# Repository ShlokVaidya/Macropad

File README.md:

# Custom Macropad  

## 🚀 Overview  
This project is a custom macropad featuring a 4x3 keyboard, 1 rotary encoders.  

## 📂 Repository Structure  
```
📁 PCB/   # KiCad PCB and schematic files
📁 docs/  # PDFs, images, and additional documentation
📁SILK/ # Logos
```
How I Built My Macropad

I designed this macropad by following a mix of online tutorials and Hack Club Blueprint resources. I first watched a few PCB design tutorials to understand how keyboard matrices, diodes, switches, and microcontrollers work together. Using those as a base, I modified the designs to match my needs — including customizing the number of keys, the layout, and the placement of the microcontroller.

- My Process

1. Research & Tutorials
I watched tutorials on KiCad basics, PCB routing, switch footprints, diode direction, and USB power protection. These helped me understand the standard keyboard wiring patterns.

2. Creating the Schematic
I made the key matrix using rows, columns, and diodes. I connected everything to the microcontroller pins according to the firmware requirements.

3. Designing the PCB Layout
Using the tutorials as reference, I arranged the switches, added stabilizing holes, routed traces, and made sure the USB and microcontroller connections followed good design practices.

4. Modifying for My Needs
I changed the layout spacing, optimized the routing, and adapted the components to the specific features I wanted in my macropad.
This included switching some pin assignments, adjusting diode placement, and improving the routing flow.

5. Final Checks
I ran ERC/DRC checks, compared my layout against multiple tutorial examples, and manually verified diode orientation and USB connections.

- Challenges I Faced

1. Learning proper keyboard matrix wiring and diode direction

2. Understanding how to route clean traces without crossing

3. Figuring out microcontroller pin assignments

4. Managing the spacing between switches

5. Ensuring USB and power connections were correct

Plans Ahead

I will start the 3D model design on December 15th

- I will then generate STL files, export renders, and add them to the README

### BOM

Cost:- https://www.digikey.in/short/rrz541t3
Spent around 6 hours around designing the pcb!

NOTE TO THE REVIEWER:
1. I have my exams upcoming so there might be a delay in designing and uploading the 3d model
2. Requesting to check the pcb connections 
3. I live in India and many parts are either not available or overpriced, it would br better if the blueprint team ship the components and pcb. No funding required them.
4. Pls do initiate tickets as I need to buy tools for the hackpad.
5. Just verify the PCB files...

Thank you,
Shlok vaidya

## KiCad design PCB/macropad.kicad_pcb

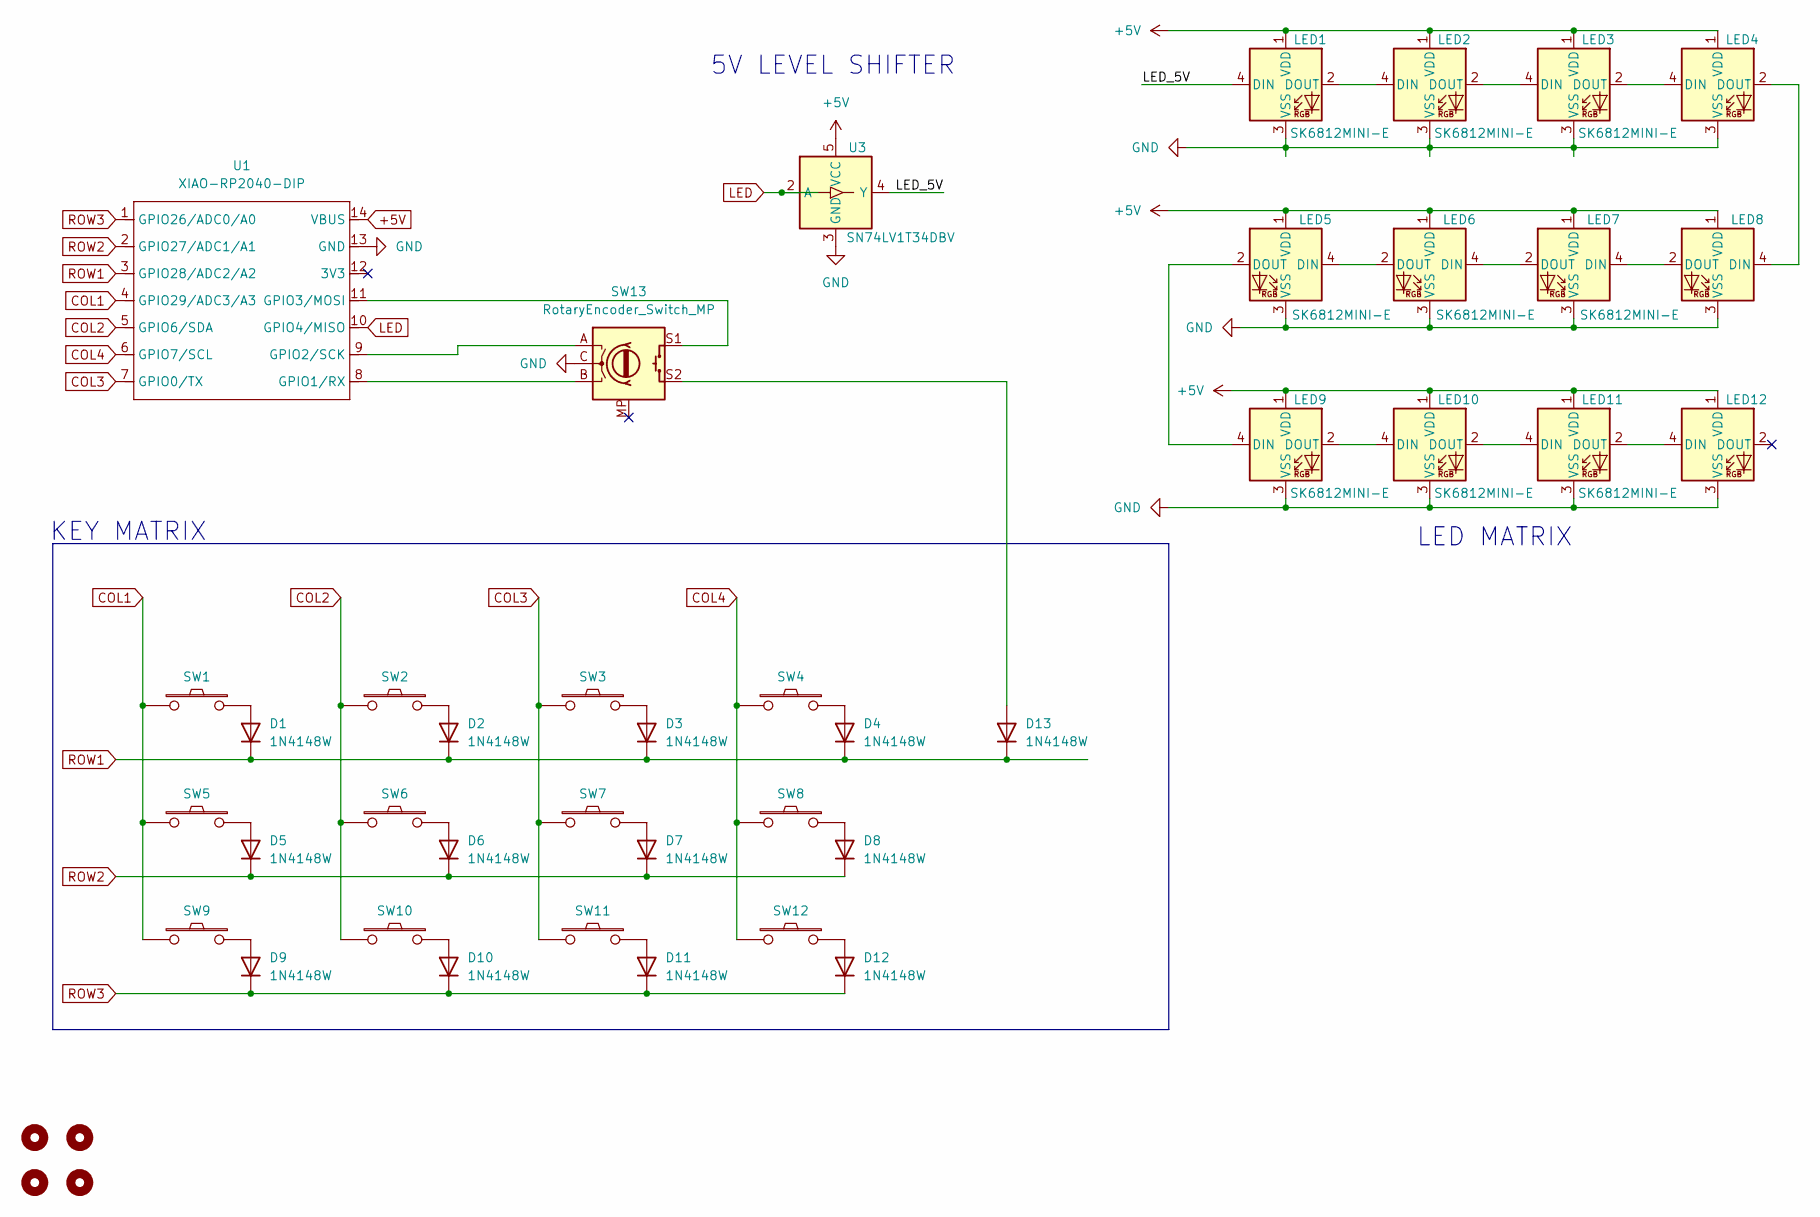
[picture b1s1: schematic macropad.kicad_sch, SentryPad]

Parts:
D1, D2, D3, D4, D5, D6, D7, D8, D9, D10, D11, D12, D13: 1N4148W; D_DO-35_SOD27_P7.62mm_Horizontal; DigiKey Part Number 1N4148W
H1, H2, H3, H4: MountingHole; Mounting_Wuerth_WA-SMSI-M3_H16mm_9774160360
LED1, LED2, LED3, LED4, LED5, LED6, LED7, LED8, LED9, LED10, LED11, LED12: SK6812MINI-E; MX_SK6812MINI-E_REV; DigiKey Part Number 1528-4960-ND
SW1, SW2, SW3, SW4, SW5, SW6, SW7, SW8, SW9, SW10, SW11, SW12: keyswitch; SW_Cherry_MX_1.00u_PCB; DigiKey Part Number MX2A-11NA
SW13: RotaryEncoder_Switch_MP; RotaryEncoder_Alps_EC11E-Switch_Vertical_H20mm
U1: XIAO-RP2040-DIP
U3: SN74LV1T34DBV; SOT-23-5; DigiKey Part Number SN74LV1T34DBV

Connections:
+5V: LED1.1 (VDD), LED2.1 (VDD), LED3.1 (VDD), LED4.1 (VDD), LED5.1 (VDD), LED6.1 (VDD), LED7.1 (VDD), LED8.1 (VDD), LED9.1 (VDD), LED10.1 (VDD), LED11.1 (VDD), LED12.1 (VDD), U1.14 (VBUS), U3.5 (VCC)
/LED_5V: LED1.4 (DIN), U3.4 (Y)
COL1: SW1.2, SW5.2, SW9.2, U1.4 (GPIO29/ADC3/A3)
COL2: SW2.2, SW6.2, SW10.2, U1.5 (GPIO6/SDA)
COL3: SW3.2, SW7.2, SW11.2, U1.7 (GPIO0/TX)
COL4: SW4.2, SW8.2, SW12.2, U1.6 (GPIO7/SCL)
GND: LED1.3 (VSS), LED2.3 (VSS), LED3.3 (VSS), LED4.3 (VSS), LED5.3 (VSS), LED6.3 (VSS), LED7.3 (VSS), LED8.3 (VSS), LED9.3 (VSS), LED10.3 (VSS), LED11.3 (VSS), LED12.3 (VSS), SW13.C, U1.13 (GND), U3.3 (GND)
LED: U1.10 (GPIO4/MISO), U3.2 (A)
unnamed: D1.2 (A), SW1.1
unnamed: D2.2 (A), SW2.1
unnamed: D3.2 (A), SW3.1
unnamed: D4.2 (A), SW4.1
unnamed: D5.2 (A), SW5.1
unnamed: D6.2 (A), SW6.1
unnamed: D7.2 (A), SW7.1
unnamed: D8.2 (A), SW8.1
unnamed: D9.2 (A), SW9.1
unnamed: D10.2 (A), SW10.1
unnamed: D11.2 (A), SW11.1
unnamed: D12.2 (A), SW12.1
unnamed: D13.2 (A), SW13.S2
unnamed: LED1.2 (DOUT), LED2.4 (DIN)
unnamed: LED2.2 (DOUT), LED3.4 (DIN)
unnamed: LED3.2 (DOUT), LED4.4 (DIN)
unnamed: LED4.2 (DOUT), LED8.4 (DIN)
unnamed: LED5.4 (DIN), LED6.2 (DOUT)
unnamed: LED5.2 (DOUT), LED9.4 (DIN)
unnamed: LED6.4 (DIN), LED7.2 (DOUT)
unnamed: LED7.4 (DIN), LED8.2 (DOUT)
unnamed: LED9.2 (DOUT), LED10.4 (DIN)
unnamed: LED10.2 (DOUT), LED11.4 (DIN)
unnamed: LED11.2 (DOUT), LED12.4 (DIN)
unnamed: SW13.B, U1.8 (GPIO1/RX)
unnamed: SW13.A, U1.9 (GPIO2/SCK)
unnamed: SW13.S1, U1.11 (GPIO3/MOSI)
ROW1: D1.1 (K), D2.1 (K), D3.1 (K), D4.1 (K), D13.1 (K), U1.3 (GPIO28/ADC2/A2)
ROW2: D5.1 (K), D6.1 (K), D7.1 (K), D8.1 (K), U1.2 (GPIO27/ADC1/A1)
ROW3: D9.1 (K), D10.1 (K), D11.1 (K), D12.1 (K), U1.1 (GPIO26/ADC0/A0)

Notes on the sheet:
LED MATRIX
KEY MATRIX
5V LEVEL SHIFTER

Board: 2 copper layers, 44 parts (13 on the bottom side), 38 nets, no tracks yet.

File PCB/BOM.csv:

"Reference","Value","Datasheet","Footprint","Qty","DNP","DigiKey Part Number"
"D1,D2,D3,D4,D5,D6,D7,D8,D9,D10,D11,D12,D13","1N4148W","~","Diode_THT:D_DO-35_SOD27_P7.62mm_Horizontal","13","","1N4148W"
"LED1,LED2,LED3,LED4,LED5,LED6,LED7,LED8,LED9,LED10,LED11,LED12","SK6812MINI-E","https://cdn-shop.adafruit.com/product-files/2686/SK6812MINI_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","XIAO_PCB:MX_SK6812MINI-E_REV","12","","1528-4960-ND"
"SW1,SW2,SW3,SW4,SW5,SW6,SW7,SW8,SW9,SW10,SW11,SW12","keyswitch","","Button_Switch_Keyboard:SW_Cherry_MX_1.00u_PCB","12","","MX2A-11NA"
"SW13","RotaryEncoder_Switch_MP","~","Rotary_Encoder:RotaryEncoder_Alps_EC11E-Switch_Vertical_H20mm","1","",""
"U1","XIAO-RP2040-DIP","","XIAO_PCB:XIAO-RP2040-DIP","1","",""
"U3","SN74LV1T34DBV","https://www.ti.com/lit/ds/symlink/sn74lv1t34.pdf","Package_TO_SOT_SMD:SOT-23-5","1","","SN74LV1T34DBV"

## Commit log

2025-11-27 Added PCB
